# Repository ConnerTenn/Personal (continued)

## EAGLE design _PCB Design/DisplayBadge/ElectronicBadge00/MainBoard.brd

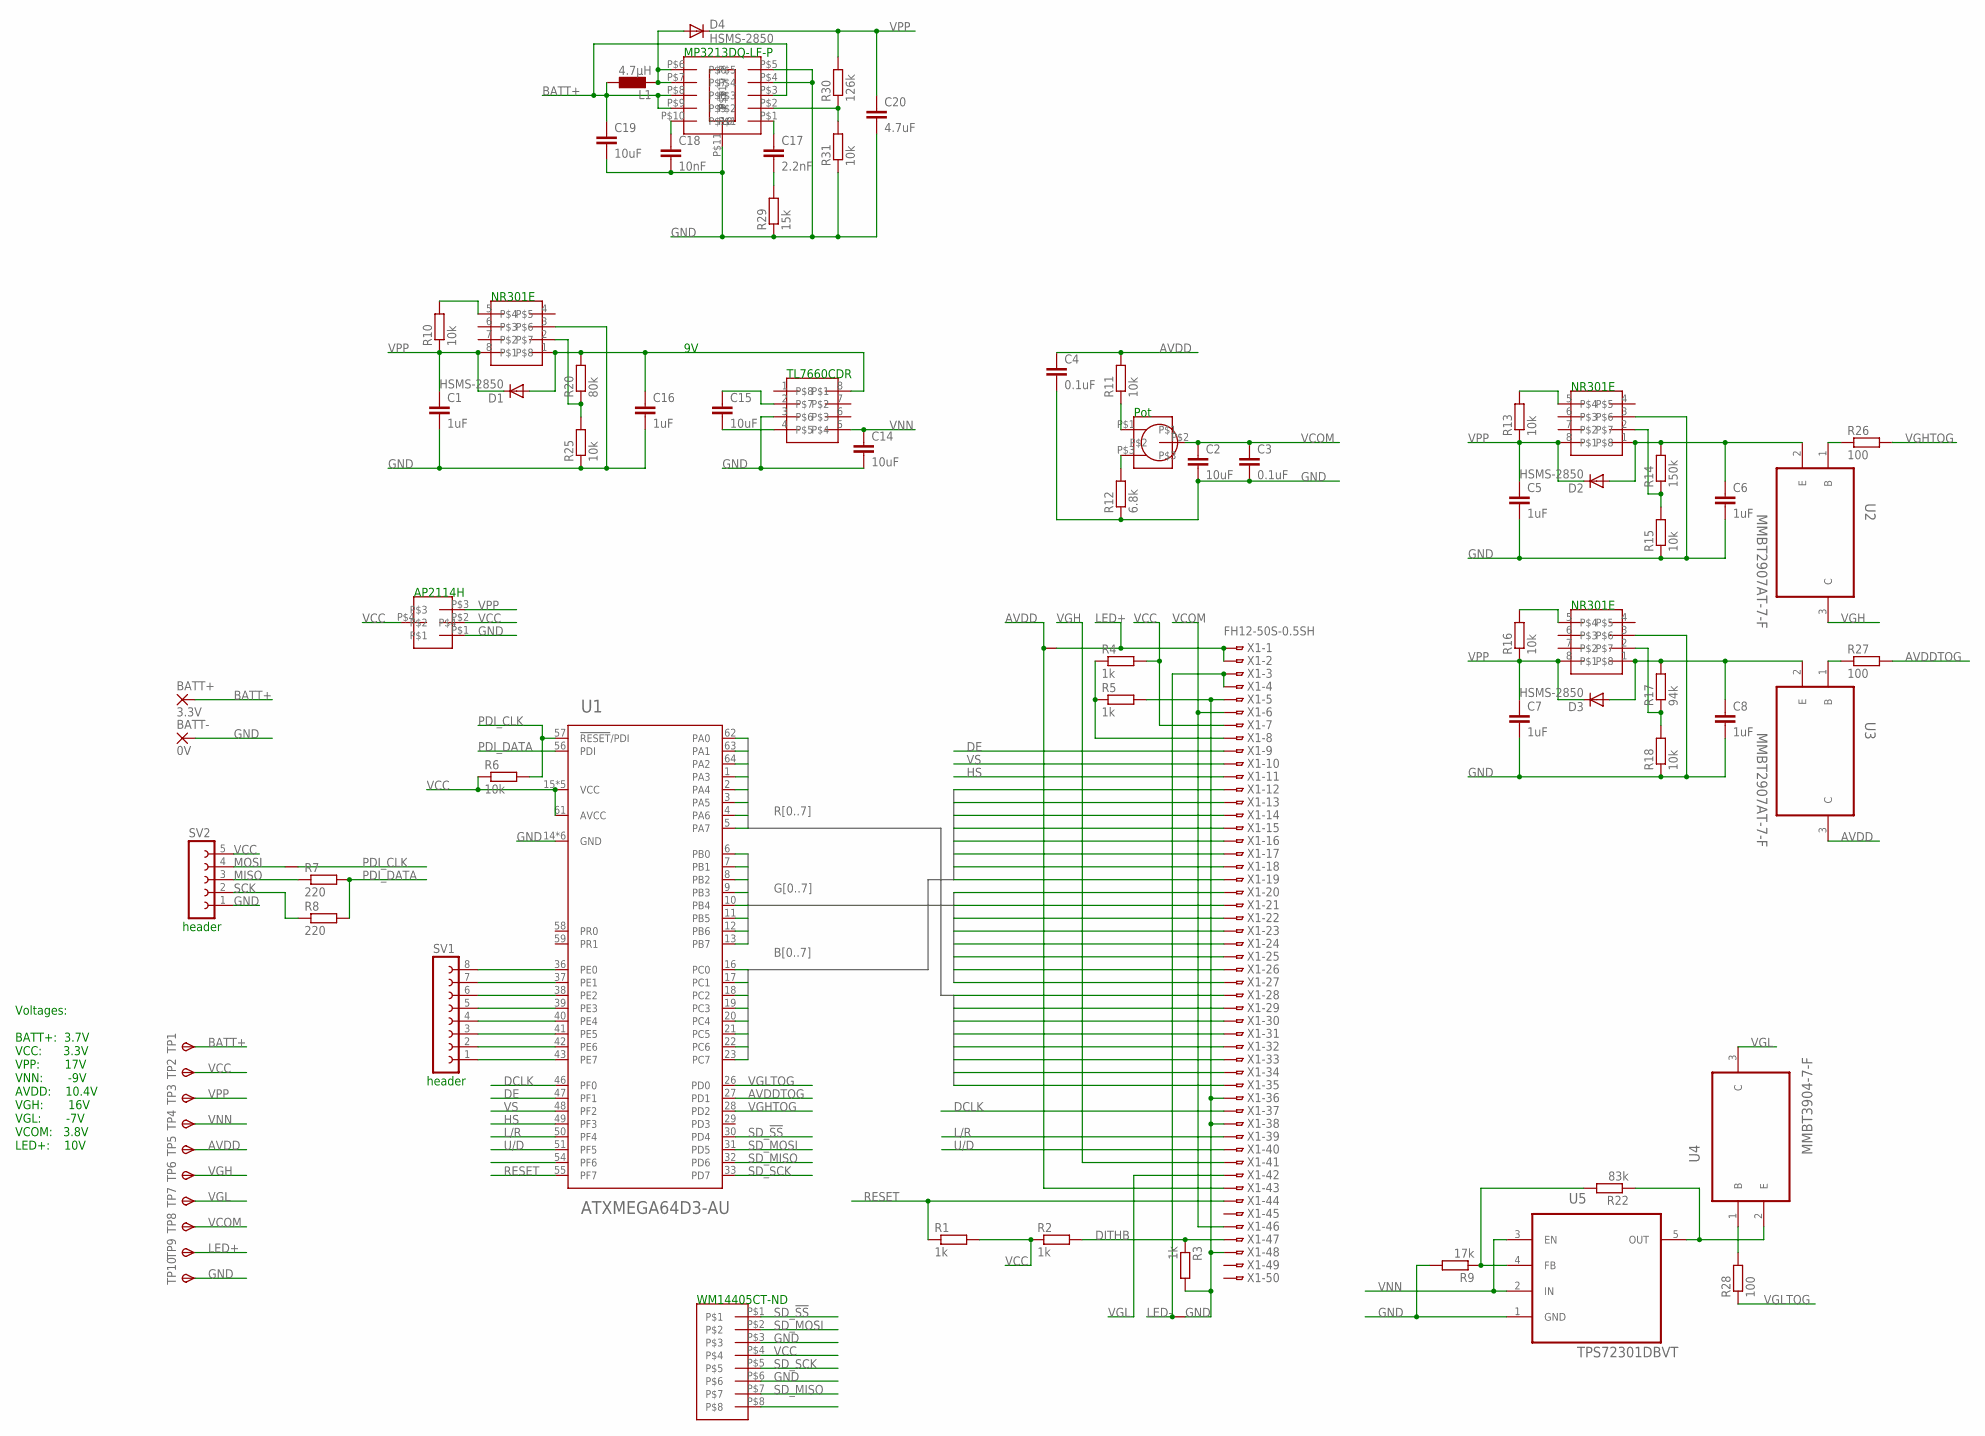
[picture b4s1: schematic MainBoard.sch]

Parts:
AP2114H: AP2114H; SOT233
BATT+: 3.3V; 2,54/1,1
BATT-: 0V; 2,54/1,1
C1, C5, C6, C7, C8, C16: 1uF; C0402
C2, C14, C15, C19: 10uF; C0402
C3, C4: 0.1uF; C0402
C17: 2.2nF; C0402
C18: 10nF; C0402
C20: 4.7uF; C0402
D1, D2, D3, D4: HSMS-2850; SOT23
L1: 4.7µH; L1812
R1, R2, R3, R4, R5: 1k; M1406
R6, R10, R11, R13, R15, R16, R18, R25, R31: 10k; M1406
R7, R8: 220; M1406
R9: 17k; M1406
R12: 6.8k; M1406
R14: 150k; M1406
R17: 94k; M1406
R20: 80k; M1406
R22: 83k; M1406
R26, R27, R28: 100; M1406
R29: 15k; M1406
R30: 126k; M1406
SV1: FE08-1; FE08
SV2: FE05-1
TP1, TP2, TP3, TP4, TP5, TP6, TP7, TP8, TP9, TP10: TPSPAD1-17Y; P1-17Y
U1: ATXMEGA64D3-AU; TQFP-64A-64
U2, U3: MMBT2907AT-7-F; SOT65P210X110-3N
U4: MMBT3904-7-F; SOT103P240X110-3N
U5: TPS72301DBVT; SOT95P280X145-5N
U$1, U$8, U$9: SHORT
U$2: MICROSD
U$4: TRIMMER; TRIMMMER
U$5, U$6, U$11: NR301E; SOIC-8
U$10: SOIC-8
U$12: QFN-10
X1: FH12-50S-0.5SH

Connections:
AVDD: C4.1, R11.2, TP5.TP, U3.3 (C), U$8.P$1, X1.43
AVDDTOG: R27.2, U1.27 (PD1)
B0: U1.16 (PC0), X1.19
B1: U1.17 (PC1), X1.18
B2: U1.18 (PC2), X1.17
B3: U1.19 (PC3), X1.16
B4: U1.20 (PC4), X1.15
B5: U1.21 (PC5), X1.14
B6: U1.22 (PC6), X1.13
B7: U1.23 (PC7), X1.12
BATT+: BATT+.1, C19.1, L1.1, TP1.TP, U$12.P$3, U$12.P$8, U$12.P$9
DCLK: U1.46 (PF0), X1.37
DE: U1.47 (PF1), X1.9
DITHB: R2.2, R3.1, X1.47
G0: U1.6 (PB0), X1.27
G1: U1.7 (PB1), X1.26
G2: U1.8 (PB2), X1.25
G3: U1.9 (PB3), X1.24
G4: U1.10 (PB4), X1.23
G5: U1.11 (PB5), X1.22
G6: U1.12 (PB6), X1.21
G7: U1.13 (PB7), X1.20
GND: AP2114H.P$1, BATT-.1, C1.2, C2.2, C3.2, C4.2, C5.2, C6.2, C7.2, C8.2, C14.2, C16.2, C18.2, C19.2, C20.2, R3.2, R5.2, R9.2, R12.1, R15.1, R18.1, R25.1, R29.1, R31.1, SV2.1, TP10.TP, U1.14 (GND), U1.24 (GND), U1.34 (GND), U1.44 (GND), U1.52 (GND), U1.60 (GND), U5.1 (GND), U$2.P$3, U$2.P$6, U$5.3, U$6.3, U$9.P$2, U$10.3, U$11.3, U$12.P$4, U$12.P$5, U$12.P$11, X1.5, X1.36, X1.38, X1.48
HS: U1.49 (PF3), X1.11
L/R: U1.50 (PF4), X1.39
LED+: TP9.TP, U$8.P$2, X1.1, X1.2
LED-: U$9.P$1, X1.3, X1.4
MISO: R7.1, SV2.3
MOSI: SV2.4, U$1.P$1
unnamed: SV1.8, U1.36 (PE0)
unnamed: R14.1, R15.2, U$5.2
unnamed: SV1.7, U1.37 (PE1)
unnamed: R11.1, U$4.P$1
unnamed: SV1.6, U1.38 (PE2)
unnamed: R12.2, U$4.P$3
unnamed: R4.1, R5.1, X1.8
unnamed: R13.2, U$5.5
unnamed: R17.1, R18.2, U$6.2
unnamed: R16.2, U$6.5
unnamed: C15.2, U$10.4
unnamed: C15.1, U$10.2
unnamed: SV1.5, U1.39 (PE3)
unnamed: R9.1, R22.2, U5.4 (FB)
unnamed: R22.1, U4.2 (E), U5.5 (OUT)
unnamed: SV1.4, U1.40 (PE4)
unnamed: SV1.3, U1.41 (PE5)
unnamed: SV1.2, U1.42 (PE6)
unnamed: SV1.1, U1.43 (PE7)
unnamed: R20.1, R25.2, U$11.2
unnamed: R10.2, U$11.5
unnamed: C6.1, D2.1 (A), R14.2, U2.2 (E), U$5.1
unnamed: C16.1, D1.1 (A), R20.2, U$10.8, U$11.1
unnamed: C8.1, D3.1 (A), R17.2, U3.2 (E), U$6.1
unnamed: R26.1, U2.1 (B)
unnamed: R27.1, U3.1 (B)
unnamed: R28.2, U4.1 (B)
unnamed: C17.1, U$12.P$1
unnamed: C17.2, R29.2
unnamed: C18.1, U$12.P$10
unnamed: D4.1 (A), L1.2, U$12.P$6, U$12.P$7
unnamed: R30.1, R31.2, U$12.P$2
PDI_CLK: R6.2, U1.57 (!RESET!/PDI), U$1.P$2
PDI_DATA: R7.2, R8.2, U1.56 (PDI)
R0: U1.62 (PA0), X1.35
R1: U1.63 (PA1), X1.34
R2: U1.64 (PA2), X1.33
R3: U1.1 (PA3), X1.32
R4: U1.2 (PA4), X1.31
R5: U1.3 (PA5), X1.30
R6: U1.4 (PA6), X1.29
R7: U1.5 (PA7), X1.28
RESET: R1.1, U1.55 (PF7), X1.44
SCK: R8.1, SV2.2
SD_!SS: U1.30 (PD4), U$2.P$1
SD_MISO: U1.32 (PD6), U$2.P$7
SD_MOSI: U1.31 (PD5), U$2.P$2
SD_SCK: U1.33 (PD7), U$2.P$5
U/D: U1.51 (PF5), X1.40
VCC: AP2114H.P$2, AP2114H.P$4, R1.2, R2.1, R4.2, R6.1, SV2.5, TP2.TP, U1.15 (VCC), U1.25 (VCC), U1.35 (VCC), U1.45 (VCC), U1.53 (VCC), U1.61 (AVCC), U$2.P$4, X1.7
VCOM: C2.1, C3.1, TP8.TP, U$4.P$2, X1.6, X1.46
VGH: TP6.TP, U2.3 (C), X1.41
VGHTOG: R26.2, U1.28 (PD2)
VGL: TP7.TP, U4.3 (C), X1.42
VGLTOG: R28.1, U1.26 (PD0)
VNN: C14.1, TP4.TP, U5.2 (IN), U5.3 (EN), U$10.5
VPP: AP2114H.P$3, C1.1, C5.1, C7.1, C20.1, D1.3 (C), D2.3 (C), D3.3 (C), D4.3 (C), R10.1, R13.1, R16.1, R30.2, TP3.TP, U$5.8, U$6.8, U$11.8
VS: U1.48 (PF2), X1.10

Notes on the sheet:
AP2114H
NR301E
Pot
WM14405CT-ND
header
Voltages: BATT+: 3.7V VCC: 3.3V VPP: 17V VNN: -9V AVDD: 10.4V VGH: 16V VGL: -7V VCOM: 3.8V LED+: 10V
TL7660CDR
MP3213DQ-LF-P

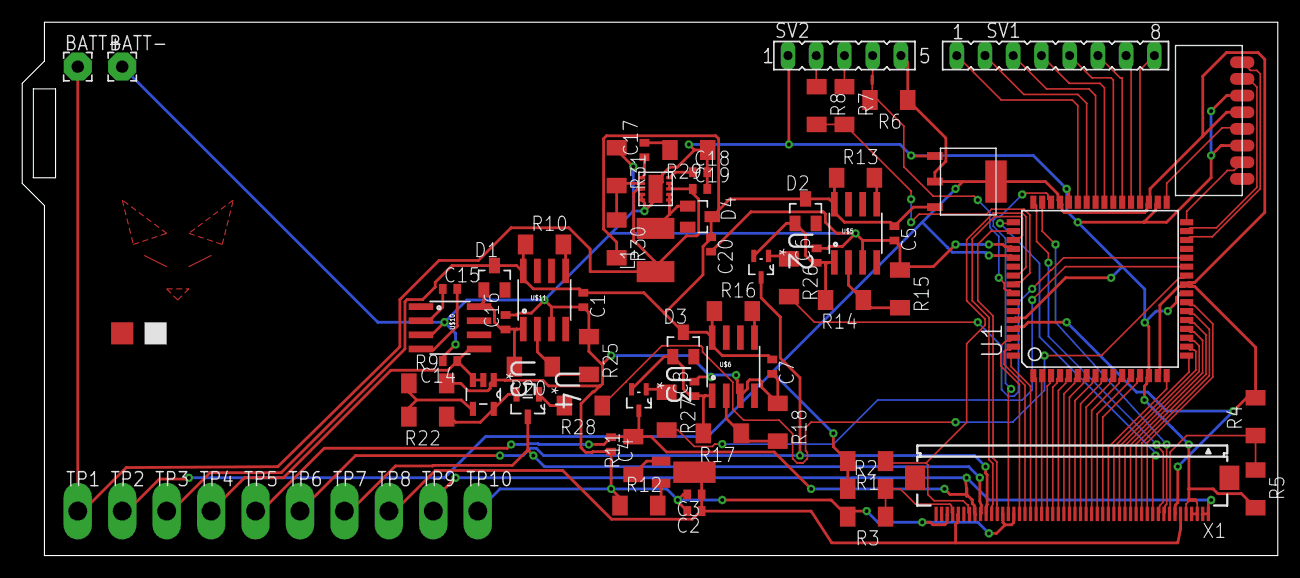
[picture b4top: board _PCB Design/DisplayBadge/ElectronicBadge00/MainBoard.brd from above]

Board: 2 copper layers, 113.0 x 48.0 mm, 78 parts (0 on the bottom side), 87 nets.

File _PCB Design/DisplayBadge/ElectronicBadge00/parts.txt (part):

Partlist

Exported from MainBoard.sch at 2017-10-10 11:33 PM

EAGLE Version 8.3.2 Copyright (c) 1988-2017 Autodesk, Inc.

Assembly variant: 

Part     Value          Device         Package           Library                                Sheet

AP2114H  AP2114H        AP2114H        SOT233            ElectronicBadge                        1
~ BATT+    3.3V           2,54/1,1       2,54/1,1          wirepad                                1
~ BATT-    0V             2,54/1,1       2,54/1,1          wirepad                                1
# C1       1uF            CC0402         C0402             eagle-ltspice                          1
# C2       10uF           CC0402         C0402             eagle-ltspice                          1
# C3       0.1uF          CC0402         C0402             eagle-ltspice                          1
# C4       0.1uF          CC0402         C0402             eagle-ltspice                          1
# C5       1uF            CC0402         C0402             eagle-ltspice                          1
# C6       1uF            CC0402         C0402             eagle-ltspice                          1
# C7       1uF            CC0402         C0402             eagle-ltspice                          1
# C8       1uF            CC0402         C0402             eagle-ltspice                          1
# C14      10uF           CC0402         C0402             eagle-ltspice                          1
# C15      10uF           CC0402         C0402             eagle-ltspice                          1
# C16      1uF            CC0402         C0402             eagle-ltspice                          1
# C17      2.2nF          CC0402         C0402             eagle-ltspice                          1
# C18      10nF           CC0402         C0402             eagle-ltspice                          1
# C19      10uF           CC0402         C0402             eagle-ltspice                          1
# C20      4.7uF          CC0402         C0402             eagle-ltspice                          1
# D1       HSMS-2850      HSMS-2850      SOT23             avago                                  1
# D2       HSMS-2850      HSMS-2850      SOT23             avago                                  1
# D3       HSMS-2850      HSMS-2850      SOT23             avago                                  1
# D4       HSMS-2850      HSMS-2850      SOT23             avago                                  1
L1       4.7µH          L              L1812             eagle-ltspice                          1
# R1       1k             R-EU_M1406     M1406             resistor                               1
# R2       1k             R-EU_M1406     M1406             resistor                               1
# R3       1k             R-EU_M1406     M1406             resistor                               1
# R4       1k             R-EU_M1406     M1406             resistor                               1
# R5       1k             R-EU_M1406     M1406             resistor                               1
# R6       10k            R-EU_M1406     M1406             resistor                               1
# R7       220            R-EU_M1406     M1406             resistor                               1
# R8       220            R-EU_M1406     M1406             resistor                               1
R9       17k            R-EU_M1406     M1406             resistor                               1
# R10      10k            R-EU_M1406     M1406             resistor                               1
# R11      10k            R-EU_M1406     M1406             resistor                               1
# R12      6.8k           R-EU_M1406     M1406             resistor                               1
# R13      10k            R-EU_M1406     M1406             resistor                               1
# R14      150k           R-EU_M1406     M1406             resistor                               1
# R15      10k            R-EU_M1406     M1406             resistor                               1
# R16      10k            R-EU_M1406     M1406             resistor                               1
R17      94k            R-EU_M1406     M1406             resistor                               1
# R18      10k            R-EU_M1406     M1406             resistor                               1
R20      80k            R-EU_M1406     M1406             resistor                               1
R22      83k            R-EU_M1406     M1406             resistor                               1
# R25      10k            R-EU_M1406     M1406             resistor                               1
# R26      100            R-EU_M1406     M1406             resistor                               1
# R27      100            R-EU_M1406     M1406             resistor                               1
# R28      100            R-EU_M1406     M1406             resistor                               1
R29      15k            R-EU_M1406     M1406             resistor                               1
R30      126k           R-EU_M1406     M1406             resistor                               1
# R31      10k            R-EU_M1406     M1406             resistor                               1
SV1                     FE08-1         FE08              con-lsta                               1
SV2                     FE05-1         FE05-1            con-lsta                               1
~ TP1      TPSPAD1-17Y    TPSPAD1-17Y    P1-17Y            testpad                                1
~ TP2      TPSPAD1-17Y    TPSPAD1-17Y    P1-17Y            testpad                                1
~ TP3      TPSPAD1-17Y    TPSPAD1-17Y    P1-17Y            testpad                                1
~ TP4      TPSPAD1-17Y    TPSPAD1-17Y    P1-17Y            testpad                                1
~ TP5      TPSPAD1-17Y    TPSPAD1-17Y    P1-17Y            testpad                                1
~ TP6      TPSPAD1-17Y    TPSPAD1-17Y    P1-17Y            testpad                                1
~ TP7      TPSPAD1-17Y    TPSPAD1-17Y    P1-17Y            testpad                                1
~ TP8      TPSPAD1-17Y    TPSPAD1-17Y    P1-17Y            testpad                                1
~ TP9      TPSPAD1-17Y    TPSPAD1-17Y    P1-17Y            testpad                                1
~ TP10     TPSPAD1-17Y    TPSPAD1-17Y    P1-17Y            testpad                                1
~ U$1      SHORT          SHORT          SHORT             ElectronicBadge                        1
# U$2      MICROSD        MICROSD        MICROSD           ElectronicBadge                        1
# U$4      TRIMMER        TRIMMER        TRIMMMER          ElectronicBadge                        1
# U$5      NR301E         SOIC-8         SOIC-8            smd-footprints                         1
# U$6      NR301E         SOIC-8         SOIC-8            smd-footprints                         1
~ U$8      SHORT          SHORT          SHORT             ElectronicBadge                        1
~ U$9      SHORT          SHORT          SHORT             ElectronicBadge                        1
# U$10     SOIC-8         SOIC-8         SOIC-8            smd-footprints                         1
#  U$11     NR301E         SOIC-8         SOIC-8            smd-footprints                         1
#  U$12     QFN-10         QFN-10         QFN-10            smd-footprints                         1
#  U1       ATXMEGA64D3-AU ATXMEGA64D3-AU TQFP-64A-64       atmel-xmega                            1
U2       MMBT2907AT-7-F MMBT2907AT-7-F SOT65P210X110-3N  Diodes_Inc_By_element14_Batch_1        1
U3       MMBT2907AT-7-F MMBT2907AT-7-F SOT65P210X110-3N  Diodes_Inc_By_element14_Batch_1        1
U4       MMBT3904-7-F   MMBT3904-7-F   SOT103P240X110-3N Diodes_Inc_By_element14_Batch_1        1
U5       TPS72301DBVT   TPS72301DBVT   SOT95P280X145-5N  Texas Instruments_By_element14_Batch_1 1
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
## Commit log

2018-01-24 Added Legacy Folder for old projects not made around git. Added first of the old programs.
2018-01-24 Lots of Additions
2018-01-24 Adding A LOT of files
2018-01-24 Clear Repository; Legacy Items moved to other repository
2018-01-24 Added Files
2018-01-24 File Upload
2018-01-25 Switched Interconnect to use git soure control instead of file copies
2018-01-25 Beginning adding support for equation structure
2018-01-25 Addtions to Equation structure
2018-01-28 Initial equation structure and equation evaluating support
2018-01-28 Renamed folder to "_CircuitMod Circuits"
2018-01-28 Modified Project to use git file versioning instead of manual versioning
2018-01-28 Added LEDArrayGlow to Personal Repository
2018-01-28 Added Reverse Polish Notation algorithm
2018-01-28 Fixed reverse polish notation algorithm issues
2018-01-28 Added support for the XOR operator
2018-01-31 Latest Upload
2018-01-31 Adding initial support for interactive command interface
2018-02-10 Added interactive command interface
2018-02-10 Fixed adding and searching glitches. removed need for VAL operator; assumed implicitly.
2018-02-10 Fixed input parsing into reversePolish (improper whitespace parsing).
2018-02-14 File Update
2018-02-14 Updated motor on/off timings
2018-02-17 Added makefile and linux compatability
2018-02-18 Auto stash before merge of "Interconnect_Working" and "origin/Interconnect_Working"
2018-02-18 Added comments and code revisions
2018-02-19 upload fix
2018-02-19 added comments
2018-02-19 comments, updates, added file Design file
2018-02-19 Initial design for next intepretor syntax
2018-03-03 Preparation for creating full input parsing. Additions to design notes and added comments
2018-03-03 Commenting out older algorithm
2018-03-04 Added Initial files. Created IV-9 Part files
2018-03-04 Connected IV-9 tubes to microcontroller
2018-03-04 Switched design to use ATTINY88 instead of ATTINY828R to gain master I2C functionality.
2018-03-04 Added RTC
2018-03-06 Added Voltage Regulator, Designed for tubes to be on second board.
2018-03-11 Sync Changes
2018-03-20 Minor additions and changes
2018-03-20 Auto stash before merge of "master" and "PocketWatch_Working"
2018-03-22 Initilizing Folders and Files
2018-03-22 Added initial structure for class
2018-03-26 Added Boost circuitry
2018-03-27 Made class template class, changed .cpp to .h for proper compilation
2018-03-27 Changed data access method from get()
2018-03-30 Completed Boost Circuitry. Slight modifications
2018-03-30 Added IO design text file
2018-03-30 Added LEDs, added switch connectors, Various Fixes
2018-03-30 Added Coin Cell
2018-03-30 Added board. Routed tubes sub-board. Fixed remaining schematic issues.
2018-03-30 Begin placement of main board. Swapped LEDs for through hole
2018-03-30 Re-routed tube board with thicker traces. Improved 3rd party board dimension accuracy.
2018-03-30 Removed 1st party boost converter.
2018-03-30 Began routing main board. Modified component placement
2018-03-30 Refined layout, routed more traces
2018-04-16 Changed Tube common to positive voltage. Changed to multiplexer design base (Frees up pins for motor control).
2018-04-16 Added Motor drive circuitry. Rearranged pin connections
2018-04-25 Migrated away from visual studio integration
2018-04-27 Cleaned up project for new revamped features
2018-04-30 Additional setup for new features. Revised design documents
